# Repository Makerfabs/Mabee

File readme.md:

# Mabee Module Serial

```c++
/*
Version:		V1.1
Author:			Vincent
Create Date:	2022/10/15
Note:
		2022/10/15	V1.1: Add readme
*/
```

[toc]

# Makerfabs

[Makerfabs home page](https://www.makerfabs.com/)

[Makerfabs Wiki](https://wiki.makerfabs.com/)

# Mabee Module List

- Mabee CO2
- Mabee 6Aixs IMU MPU6050
- Mabee Button
- Mabee DHT11 sensor
- Mabee Relay 10A
- Mabee Serial WiFi
- Mabee Servo SG90
- Mabee Slide Potentimeter
- Mabee WS2812 8bit

## Mabee CO2

This Mabee module is an air quality monitor. Based on SGP30, this module provides TVOC(Total Volatile Organic Compounds) and CO2eq output; Based on the Sensirion temperature/ humidity sensors SHT31, it output highest-accuracy ±2% relative humidity and ±0.3°C accuracy temperature.

Product Link ：[Mabee_TVOC and eCO2 SGP30 & Temperature and Humidity SHT31](https://www.makerfabs.com/mabee-tvoc-and-eco2-sgp30-sht31.html)

Wiki Link : [Mabee_CO2](https://wiki.makerfabs.com/Mabee_CO2.html)

## Mabee 6Aixs IMU MPU6050

This Mabee_ MPU6050 Accelerometer& Gyro has 3-Axis digital accelerometer and 3-Axis gyroscope, suitable for common motion capturing of acceleration and Orientation.

Product Link ：[Mabee_6Aixs IMU MPU6050](https://www.makerfabs.com/mabee-6aixs-imu-mpu6050.html)

## Mabee Button

A simple button with Cap for digital inputs, with Mabee Interface for easy usage.

Product Link ：[Mabee_Button](https://www.makerfabs.com/mabee-button.html)

## Mabee DHT11 sensor

Mabee_Temperature& Humidity DHT11 is high quality, low-cost digital temperature, and humidity sensor based on the DHT11 module, which is the most commonly used sensor for temperature& Humidity, it is widely favored by hardware enthusiasts for its advantages such as low power consumption and excellent long-term stability.

Product Link ：[Mabee_Temperature& Humidity DHT11](https://www.makerfabs.com/mabee-dht11.html)

## Mabee Relay 10A

A Relay module used to control high voltage& big current circuits On/Off. It is a digital normally open switch that controls a relay capable of switching much higher voltages and currents than your normal Arduino boards. When the relay is switched on, the LED will light up and the relay will allow current to flow. The peak voltage capability is 250V at 10A.

Product Link ：[Mabee_Relay 10A](https://www.makerfabs.com/mabee-relay-10a.html)

## Mabee Serial WiFi

This Mabee Serial Wifi is based on ESP-12S, to make the WiFi available for more hardware platforms such as the Pi Pico.

Product Link ：[Mabee_Serial WiFi](https://www.makerfabs.com/mabee-serial-wifi.html)

## Mabee Servo SG90

A simple& cheap Servo module with Mabee interface, for starters to learn the servo usage and basic applications.

Product Link ：[Mabee_Servo SG90](https://www.makerfabs.com/mabee-servo-sg90.html)

## Mabee Slide Potentimeter

Do you still remember your physics class in junior middle school, about the potentiometer? The slide potentiometer could be the most basic impression for a "potentiometer".

Product Link ：[Mabee_Slide Potentiometer](https://www.makerfabs.com/mabee-slide-potentiometer.html)

## Mabee WS2812 8bit

8 pcs of WS2812 RGB LED easily for panel mounting with Mabee interface. 2 Mabee interface Input& Output, for multiple cascading.

Product Link ：[Mabee_WS2812_8bit](https://www.makerfabs.com/mabee-ws2812-8bit.html)

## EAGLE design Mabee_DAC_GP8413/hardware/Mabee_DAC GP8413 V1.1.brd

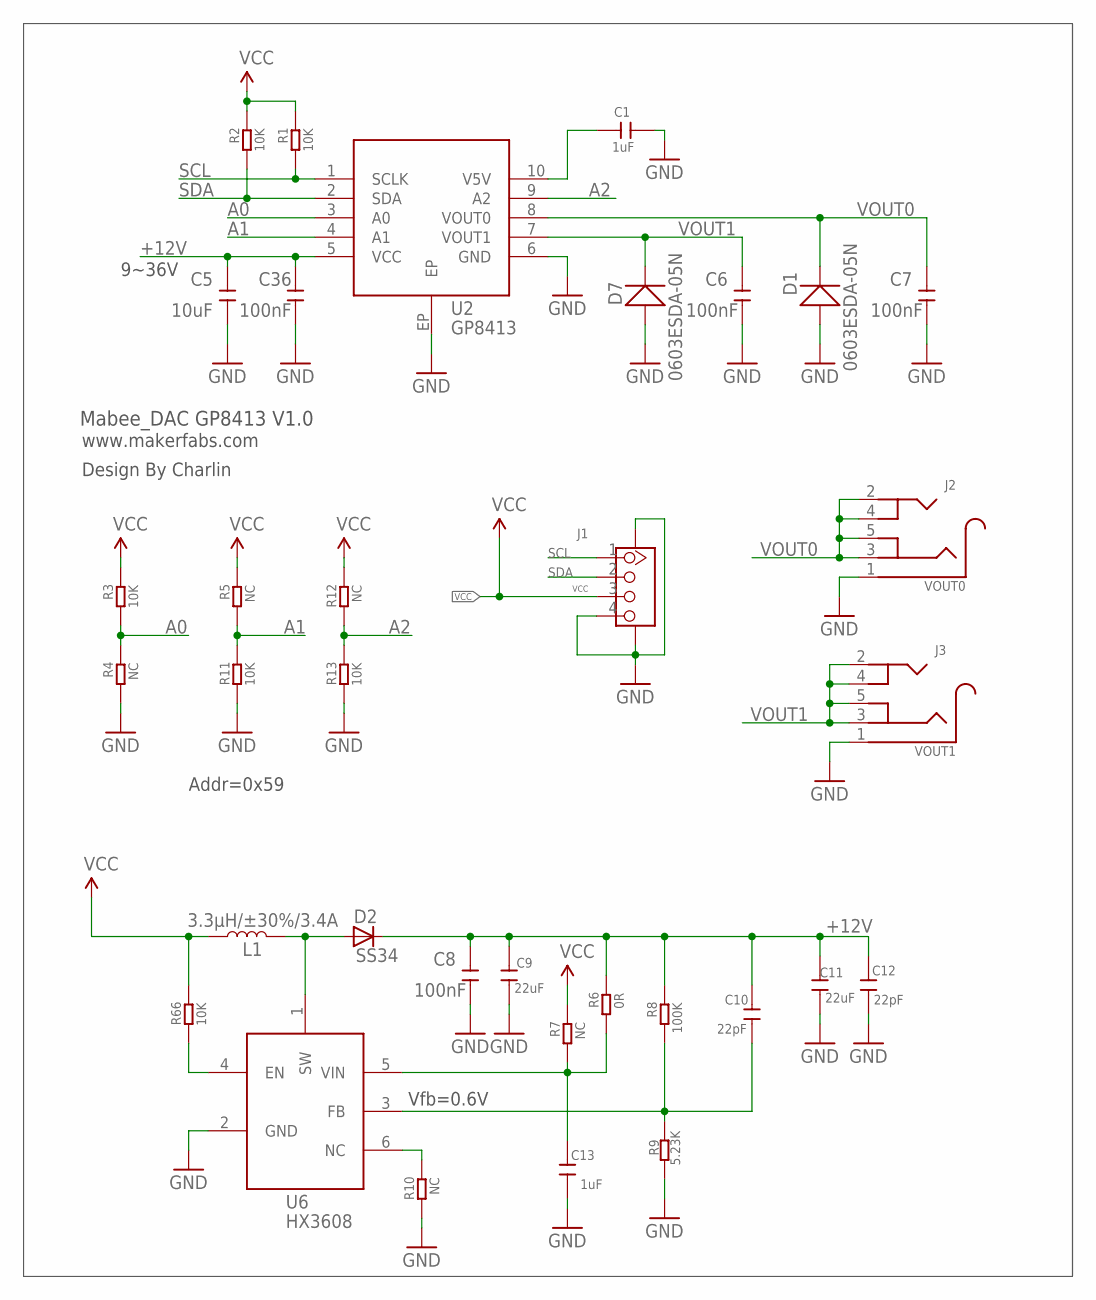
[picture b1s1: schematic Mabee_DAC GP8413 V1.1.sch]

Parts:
C1, C13: 1uF; 0603
C5: 10uF; 0603
C6, C7, C8, C36: 100nF; 0603
C9, C11: 22uF; DISCRETE_C0805
C10, C12: 22pF; 0603
D1, D7: 0603ESDA-05N; DISCRETE_SOD523
D2: SS34; DO-214AC
J1: GROVE-CONNECTOR-SMD'90D'; HW4-SMD-2.0-90D
L1: 3.3µH/±30%/3.4A; CR54
R1, R2, R3, R11, R13, R66: 10K; R0603
R4, R5, R7, R10, R12: NC; R0603
R6: 0R; R0603
R8: 100K; R0603
R9: 5.23K; R0603
U2: GP8413; ESOP-10-EP-150MIL
U6: HX3608; SOT-23-6
VOUT0: J2; 4UCONN_19269
VOUT1: J3; 4UCONN_19269

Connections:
+12V: C5.2, C8.2, C9.2, C10.2, C11.2, C12.2, C36.2, D2.C, R6.2, R8.2, U2.5 (VCC)
A0: R3.1, R4.2, U2.3 (A0)
A1: R5.1, R11.2, U2.4 (A1)
A2: R12.1, R13.2, U2.9 (A2)
ENABLE: R66.1, U6.4 (EN)
GND: C1.1, C5.1, C6.1, C7.1, C8.1, C9.1, C11.1, C12.1, C13.1, C36.1, D1.+, D7.+, J1.4, J1.SS1, J1.SS2, R4.1, R9.1, R10.1, R11.1, R13.1, U2.6 (GND), U2.EP, U6.2 (GND), VOUT0.1, VOUT1.1
unnamed: C1.2, U2.10 (V5V)
unnamed: C13.2, R6.1, R7.1, U6.5 (VIN)
unnamed: C10.1, R8.1, R9.2, U6.3 (FB)
unnamed: R10.2, U6.6 (NC)
unnamed: D2.A, L1.P$2 (2), U6.1 (SW)
SCL: J1.1, R1.1, U2.1 (SCLK)
SDA: J1.2, R2.1, U2.2 (SDA)
VCC: J1.3, L1.P$1 (1), R1.2, R2.2, R3.2, R5.2, R7.2, R12.2, R66.2
VOUT0: C7.2, D1.-, U2.8 (VOUT0), VOUT0.2, VOUT0.3, VOUT0.4, VOUT0.5
VOUT1: C6.2, D7.-, U2.7 (VOUT1), VOUT1.2, VOUT1.3, VOUT1.4, VOUT1.5

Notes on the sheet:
Mabee_DAC GP8413 V1.0
www.makerfabs.com
Vfb=0.6V
9~36V
Addr=0x59
Design By Charlin

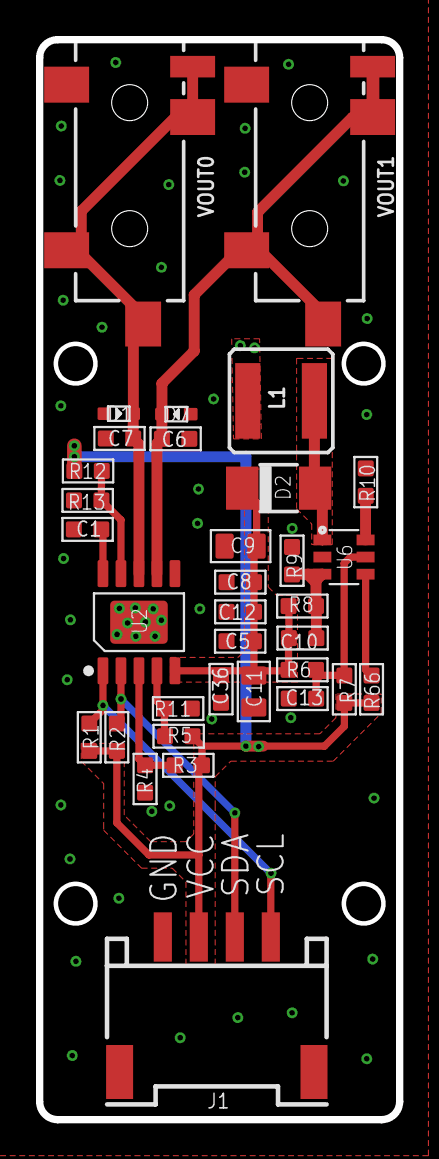
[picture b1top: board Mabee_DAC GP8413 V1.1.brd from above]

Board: 2 copper layers, 20.0 x 60.0 mm, 35 parts (1 on the bottom side), 16 nets.

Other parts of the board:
U$1: MAKERFABS_0.3

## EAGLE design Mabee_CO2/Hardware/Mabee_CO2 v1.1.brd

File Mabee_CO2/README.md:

# Mabee_CO2
Mabee_TVOC and eCO2 SGP30 &amp; Temperature and Humidity SHT31

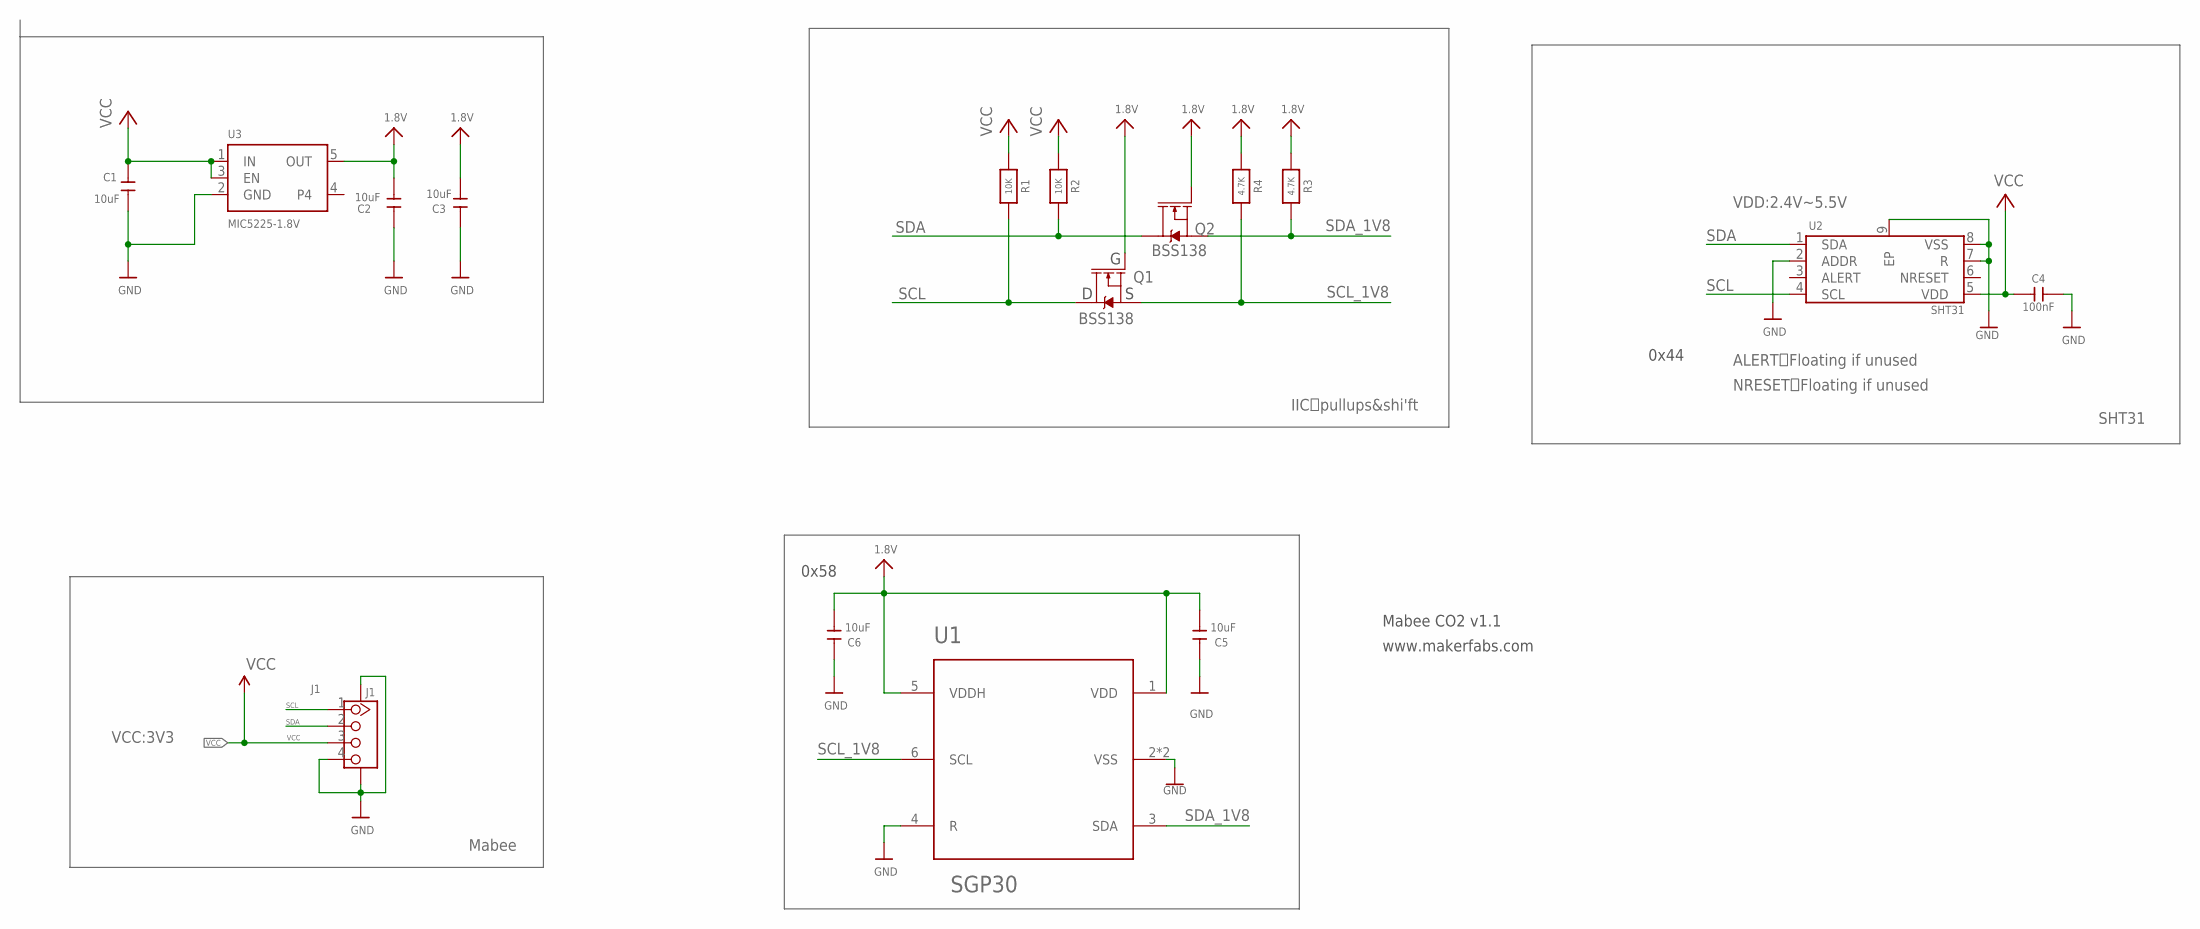
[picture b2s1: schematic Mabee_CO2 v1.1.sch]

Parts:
C1, C2, C3, C5, C6: 10uF; 0603
C4: 100nF; 0603
J1: J1; HW4-SMD-2.0-90D
Q1, Q2: BSS138; SOT23-3
R1, R2: 10K; 0603-NO
R3, R4: 4.7K; 0603-NO
U1: SGP30
U2: SHT31; DFN-8(3X3)_EP
U3: MIC5225-1.8V; SOT23-5

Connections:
1.8V: C2.1, C3.1, C5.1, C6.1, Q1.1 (G), Q2.1 (G), R3.1, R4.1, U1.1 (VDD), U1.5 (VDDH), U3.5 (OUT)
GND: C1.2, C2.2, C3.2, C4.2, C5.2, C6.2, J1.4, J1.SS1, J1.SS2, U1.2 (VSS), U1.4 (R), U1.P$7 (VSS), U2.2 (ADDR), U2.7 (R), U2.8 (VSS), U2.9 (EP), U3.2 (GND)
SCL: J1.1, Q1.3 (D), R1.2, U2.4 (SCL)
SCL_1V8: Q1.2 (S), R4.2, U1.6 (SCL)
SDA: J1.2, Q2.3 (D), R2.2, U2.1 (SDA)
SDA_1V8: Q2.2 (S), R3.2, U1.3 (SDA)
VCC: C1.1, C4.1, J1.3, R1.1, R2.1, U2.5 (VDD), U3.1 (IN), U3.3 (EN)

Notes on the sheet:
Mabee
SHT31
IIC pullups&shi'ft
Mabee CO2 v1.1
www.makerfabs.com
VCC:3V3
VDD:2.4V~5.5V
ALERT：Floating if unused
NRESET：Floating if unused
0x58
0x44

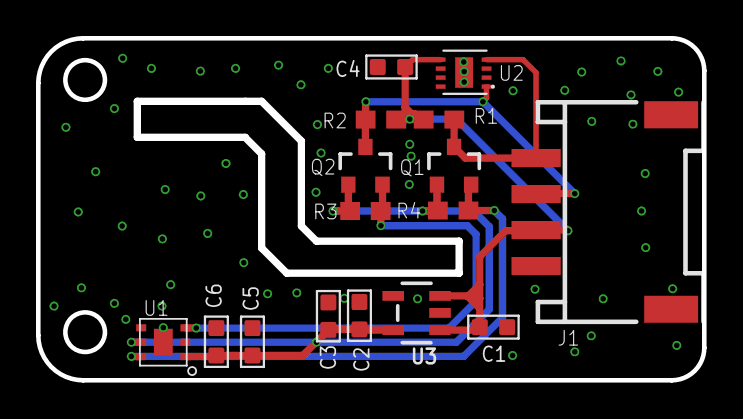
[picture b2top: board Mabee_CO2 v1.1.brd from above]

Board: 2 copper layers, 36.8 x 18.8 mm, 17 parts (1 on the bottom side), 7 nets.

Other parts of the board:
U$10: MAKERFABS_0.3

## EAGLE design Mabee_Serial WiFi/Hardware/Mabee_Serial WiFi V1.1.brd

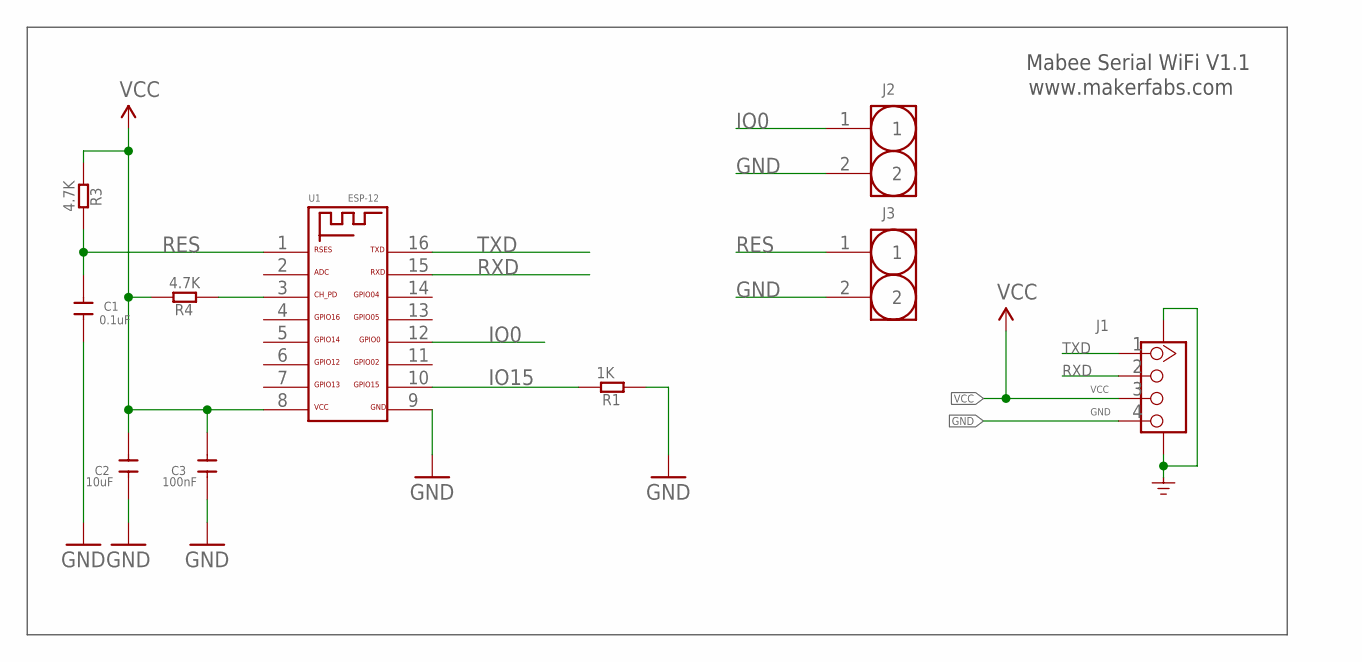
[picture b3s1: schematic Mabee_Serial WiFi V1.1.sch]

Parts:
C1: 0.1uF; C0603
C2: 10uF; C0603
C3: 100nF; C0603
J1: GROVE-CONNECTOR-SMD'90D'; HW4-SMD-2.0-90D
J2, J3: HEADER-2P-65/35MIL; 2P-2.54-65/35MIL
R1: 1K; 0603
R3, R4: 4.7K; 0603
U1: ESP-12

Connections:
EN: R4.1, U1.3
GND: C1.2, C2.2, C3.2, J1.4, J1.SS1, J1.SS2, J2.2, J3.2, R1.1, U1.9
IO0: J2.1, U1.12
IO15: R1.2, U1.10
RES: C1.1, J3.1, R3.2, U1.1
RXD: J1.2, U1.15
TXD: J1.1, U1.16
VCC: C2.1, C3.1, J1.3, R3.1, R4.2, U1.8

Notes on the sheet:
Mabee Serial WiFi V1.1
www.makerfabs.com

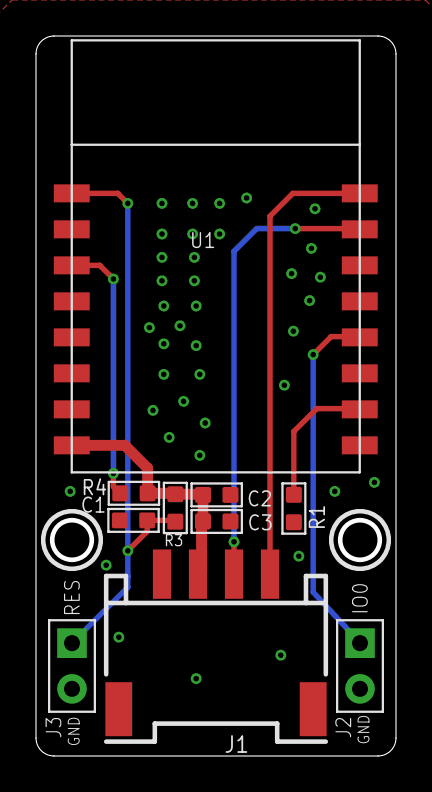
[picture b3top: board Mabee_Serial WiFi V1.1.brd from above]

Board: 2 copper layers, 19.7 x 39.7 mm, 11 parts (1 on the bottom side), 8 nets.

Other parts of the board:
U$2: MAKERFABS_0.3

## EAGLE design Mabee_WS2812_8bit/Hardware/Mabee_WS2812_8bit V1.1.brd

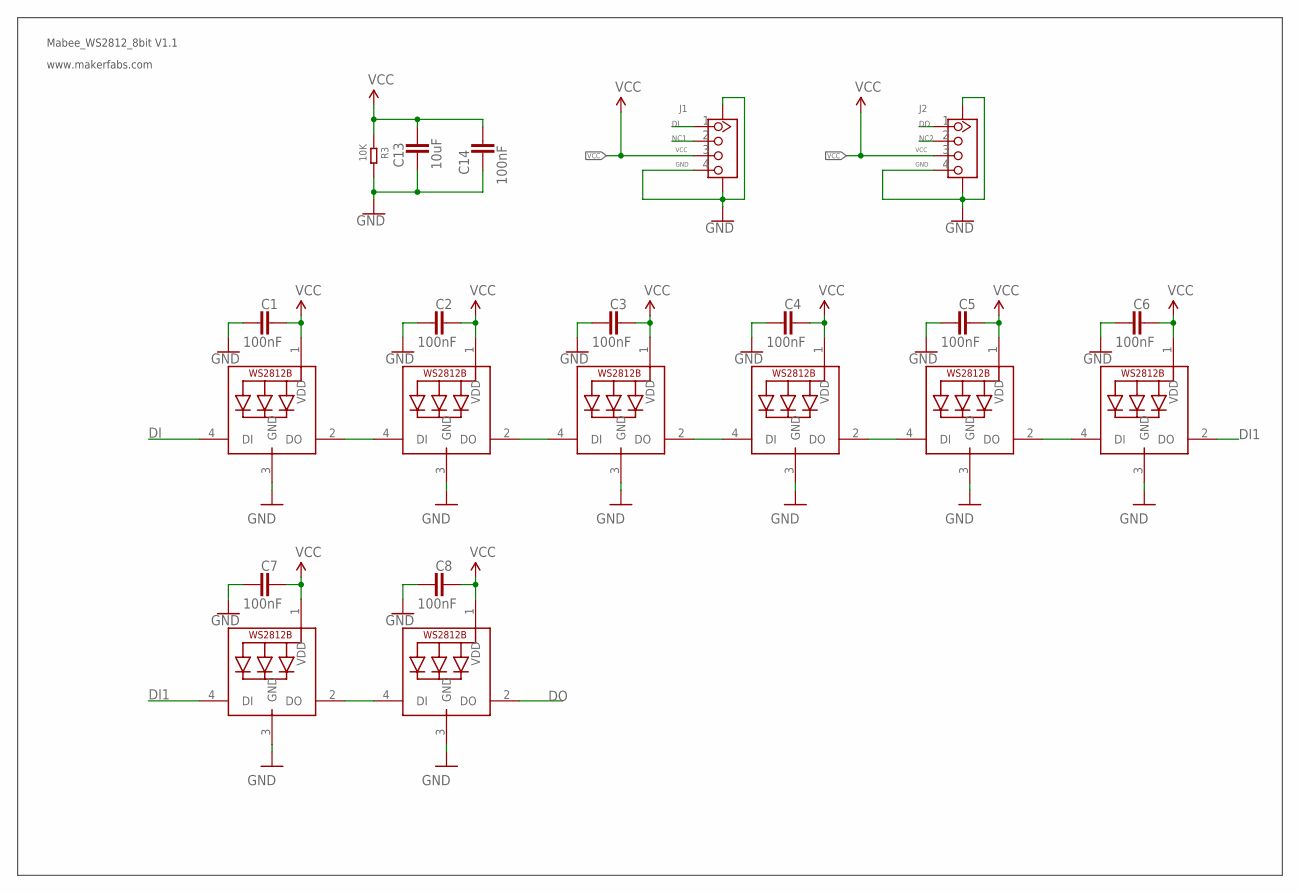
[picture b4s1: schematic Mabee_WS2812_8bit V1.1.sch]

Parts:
C1, C2, C3, C4, C5, C6, C7, C8, C14: 100nF; C0603
C13: 10uF; C0603
J1, J2: GROVE-CONNECTOR-SMD'90D'; HW4-SMD-2.0-90D
LED0, LED1, LED2, LED3, LED4, LED5, LED6, LED7: WS2812B3535; LED3535
R3: 10K; R0603

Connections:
DI: J1.1, LED0.4 (DI)
DI1: LED5.2 (DO), LED6.4 (DI)
DO: J2.1, LED7.2 (DO)
GND: C1.1, C2.1, C3.1, C4.1, C5.1, C6.1, C7.1, C8.1, C13.1, C14.1, J1.4, J1.SS1, J1.SS2, J2.4, J2.SS1, J2.SS2, LED0.3 (GND), LED1.3 (GND), LED2.3 (GND), LED3.3 (GND), LED4.3 (GND), LED5.3 (GND), LED6.3 (GND), LED7.3 (GND), R3.2
unnamed: LED0.2 (DO), LED1.4 (DI)
unnamed: LED1.2 (DO), LED2.4 (DI)
unnamed: LED2.2 (DO), LED3.4 (DI)
unnamed: LED3.2 (DO), LED4.4 (DI)
unnamed: LED4.2 (DO), LED5.4 (DI)
unnamed: LED6.2 (DO), LED7.4 (DI)
NC1: J1.2
NC2: J2.2
VCC: C1.2, C2.2, C3.2, C4.2, C5.2, C6.2, C7.2, C8.2, C13.2, C14.2, J1.3, J2.3, LED0.1 (VDD), LED1.1 (VDD), LED2.1 (VDD), LED3.1 (VDD), LED4.1 (VDD), LED5.1 (VDD), LED6.1 (VDD), LED7.1 (VDD), R3.1

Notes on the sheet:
Mabee_WS2812_8bit V1.1
www.makerfabs.com

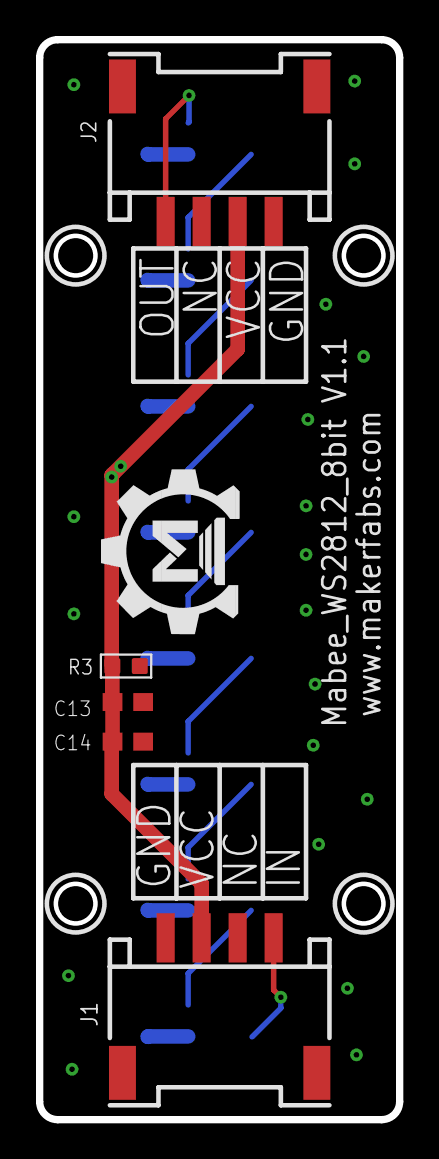
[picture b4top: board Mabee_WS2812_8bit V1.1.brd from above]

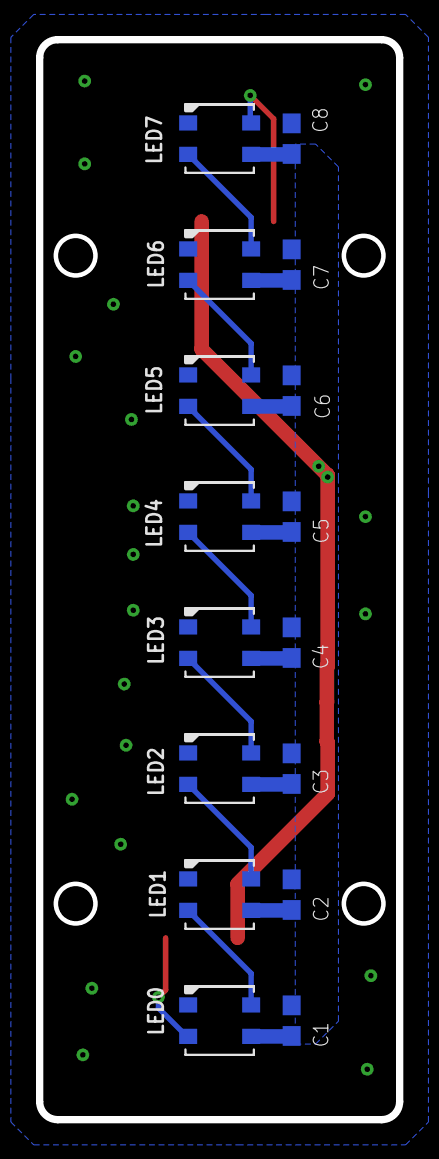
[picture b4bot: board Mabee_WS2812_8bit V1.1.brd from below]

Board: 2 copper layers, 20.0 x 60.0 mm, 22 parts (16 on the bottom side), 11 nets.

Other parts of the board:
U$2: MAKERFABS_0.3

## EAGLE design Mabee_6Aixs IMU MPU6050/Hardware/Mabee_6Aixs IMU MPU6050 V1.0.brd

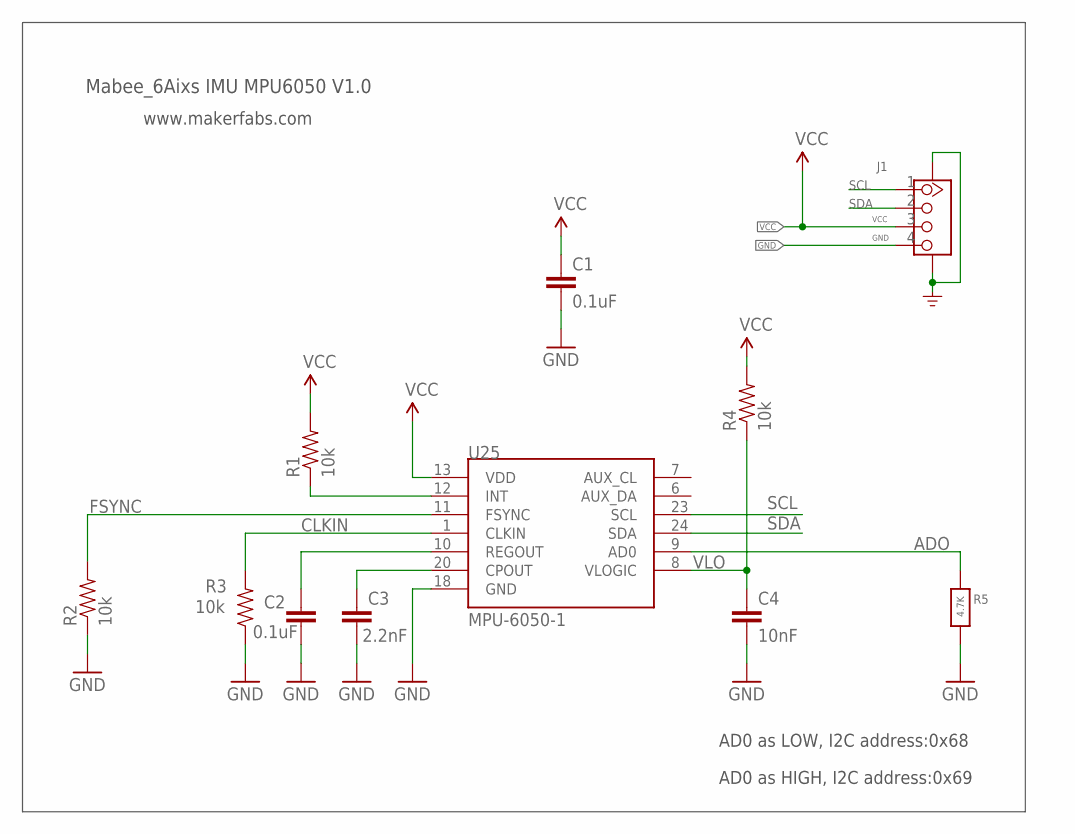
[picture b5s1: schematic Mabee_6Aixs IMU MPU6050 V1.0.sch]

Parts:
C1, C2: 0.1uF; 0603-CAP
C3: 2.2nF; 0603-CAP
C4: 10nF; 0603-CAP
J1: GROVE-CONNECTOR-SMD'90D'; HW4-SMD-2.0-90D
R1, R2, R3, R4: 10k; 0603-RES
R5: 4.7K; 0603-NO
U25: MPU-6050-1; QFN-24-4MM2

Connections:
ADO: R5.1, U25.9 (AD0)
CLKIN: R3.2, U25.1 (CLKIN)
FSYNC: R2.2, U25.11 (FSYNC)
GND: C1.2, C2.2, C3.2, C4.2, J1.4, J1.SS1, J1.SS2, R2.1, R3.1, R5.2, U25.18 (GND)
IO35: R1.1, U25.12 (INT)
unnamed: C3.1, U25.20 (CPOUT)
unnamed: C2.1, U25.10 (REGOUT)
SCL: J1.1, U25.23 (SCL)
SDA: J1.2, U25.24 (SDA)
VCC: C1.1, J1.3, R1.2, R4.2, U25.13 (VDD)
VLO: C4.1, R4.1, U25.8 (VLOGIC)

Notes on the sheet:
Mabee_6Aixs IMU MPU6050 V1.0
AD0 as LOW, I2C address:0x68
AD0 as HIGH, I2C address:0x69
www.makerfabs.com

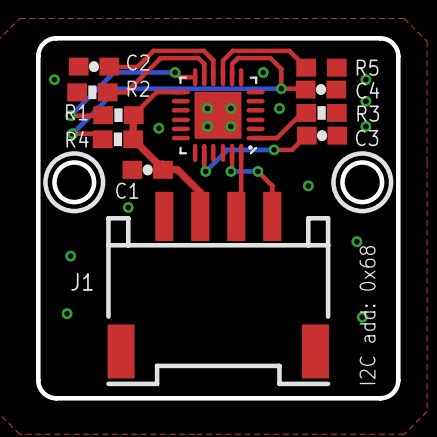
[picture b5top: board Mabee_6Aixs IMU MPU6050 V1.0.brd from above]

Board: 2 copper layers, 20.0 x 20.0 mm, 12 parts (1 on the bottom side), 11 nets.

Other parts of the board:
U$1: MAKERFABS_0.3

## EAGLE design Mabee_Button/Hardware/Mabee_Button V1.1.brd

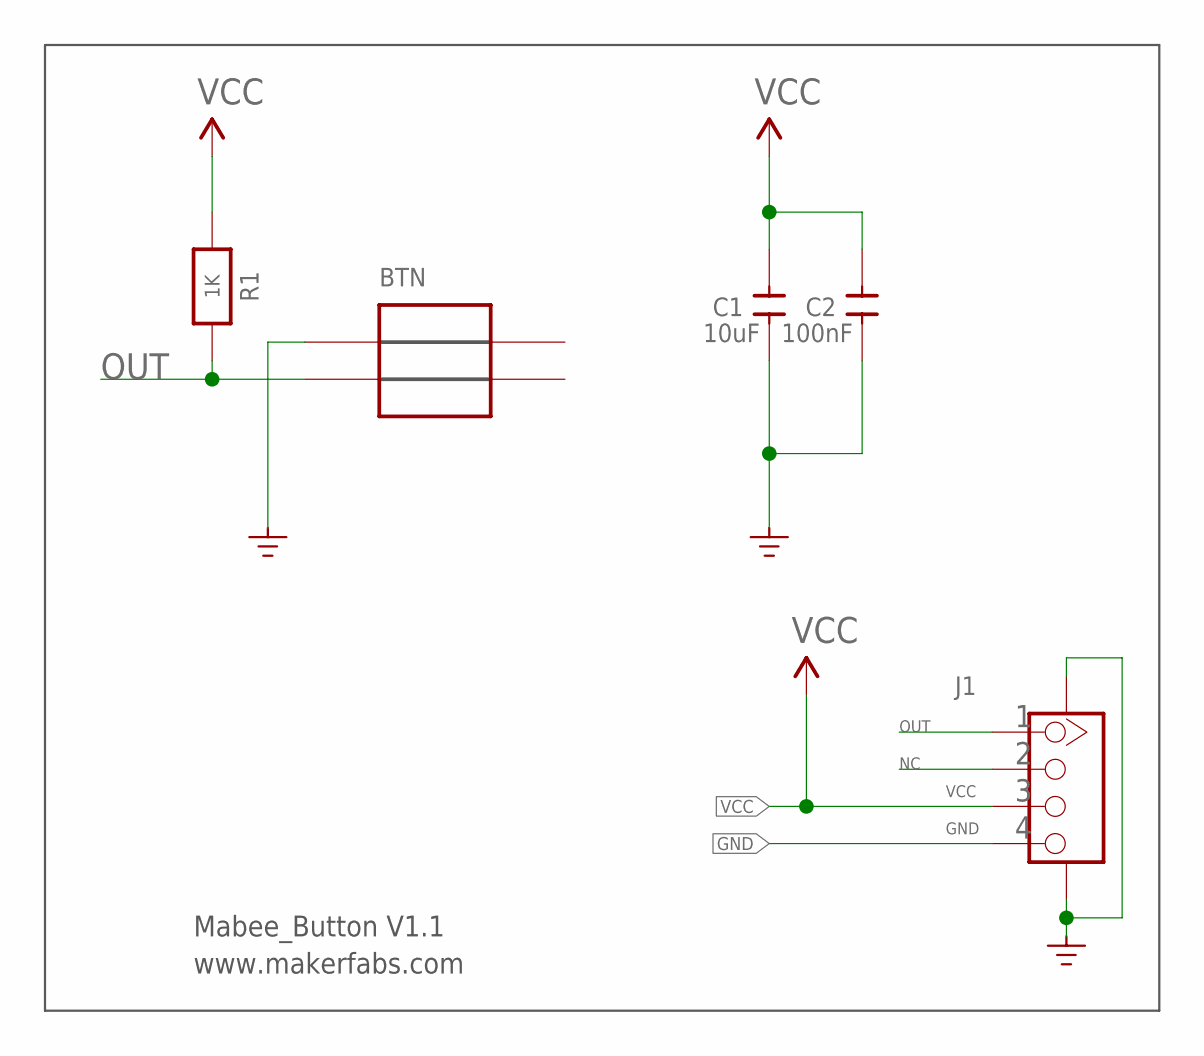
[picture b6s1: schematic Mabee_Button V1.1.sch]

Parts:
BTN: BUTTON_1212; 12*12_BUTTON_DIP
C1: 10uF; 0603
C2: 100nF; 0603
J1: GROVE-CONNECTOR-SMD'90D'; HW4-SMD-2.0-90D
R1: 1K; 0603-NO

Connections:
GND: BTN.1, C1.1, C2.1, J1.4, J1.SS1, J1.SS2
NC: J1.2
OUT: BTN.3, J1.1, R1.2
VCC: C1.2, C2.2, J1.3, R1.1

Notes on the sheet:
Mabee_Button V1.1
www.makerfabs.com

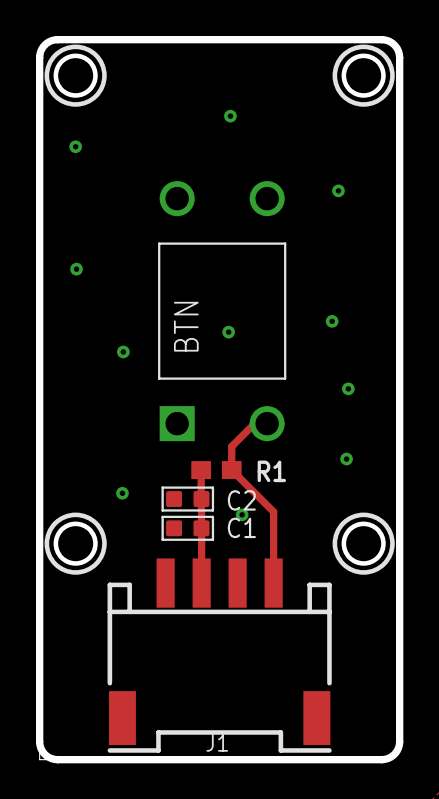
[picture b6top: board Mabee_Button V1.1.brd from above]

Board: 2 copper layers, 20.0 x 40.0 mm, 6 parts (1 on the bottom side), 3 nets.

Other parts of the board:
U$3: MAKERFABS_0.3

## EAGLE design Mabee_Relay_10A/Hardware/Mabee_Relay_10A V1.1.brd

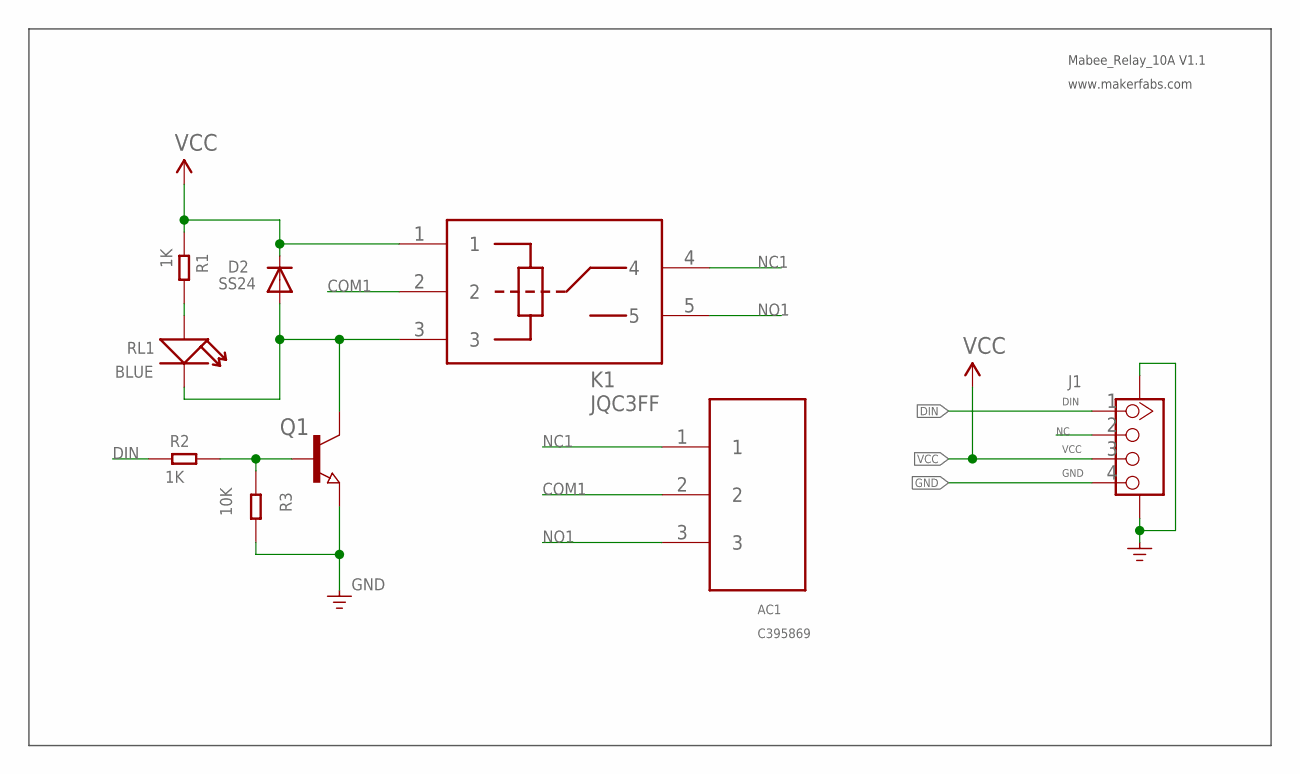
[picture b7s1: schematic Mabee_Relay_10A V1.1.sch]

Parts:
AC1: C395869; PIN_3P
D2: SS24; SMADIODE
J1: GROVE-CONNECTOR-SMD'90D'; HW4-SMD-2.0-90D
K1: JQC3FF; DIP5_JQC3FF
Q1: NPN-TRANSISTOR_SOT23; SOT23
R1, R2: 1K; R0603
R3: 10K; R0603
RL1: BLUE; LED-0603

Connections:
COM1: AC1.2, K1.2
DIN: J1.1, R2.1
GND: J1.4, J1.SS1, J1.SS2, Q1.2 (E), R3.2
unnamed: R1.2, RL1.+
unnamed: D2.A, K1.3, Q1.3 (C), RL1.-
unnamed: Q1.1 (B), R2.2, R3.1
NC: J1.2
NC1: AC1.1, K1.4
NO1: AC1.3, K1.5
VCC: D2.C, J1.3, K1.1, R1.1

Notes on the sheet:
Mabee_Relay_10A V1.1
www.makerfabs.com

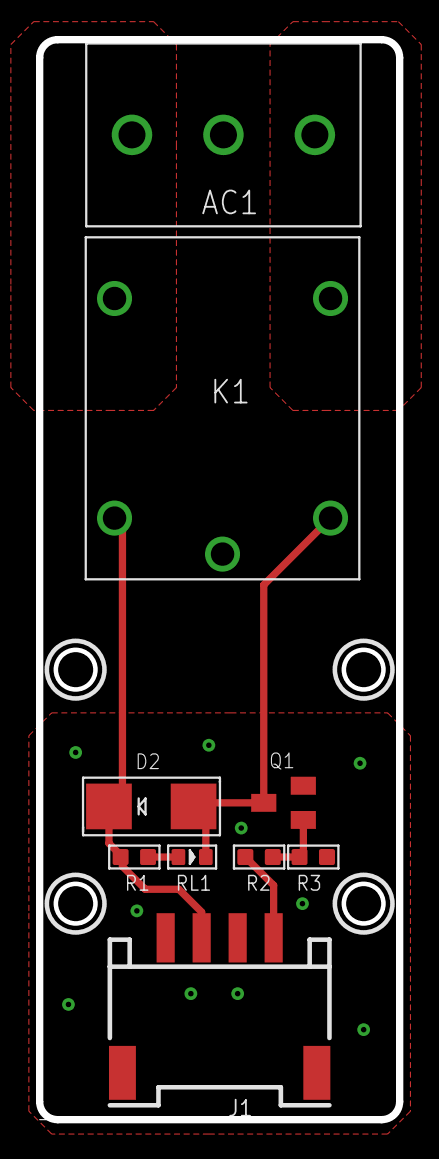
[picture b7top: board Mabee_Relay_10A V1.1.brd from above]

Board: 2 copper layers, 20.0 x 60.0 mm, 10 parts (1 on the bottom side), 9 nets.

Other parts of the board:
U$2: MAKERFABS_0.3

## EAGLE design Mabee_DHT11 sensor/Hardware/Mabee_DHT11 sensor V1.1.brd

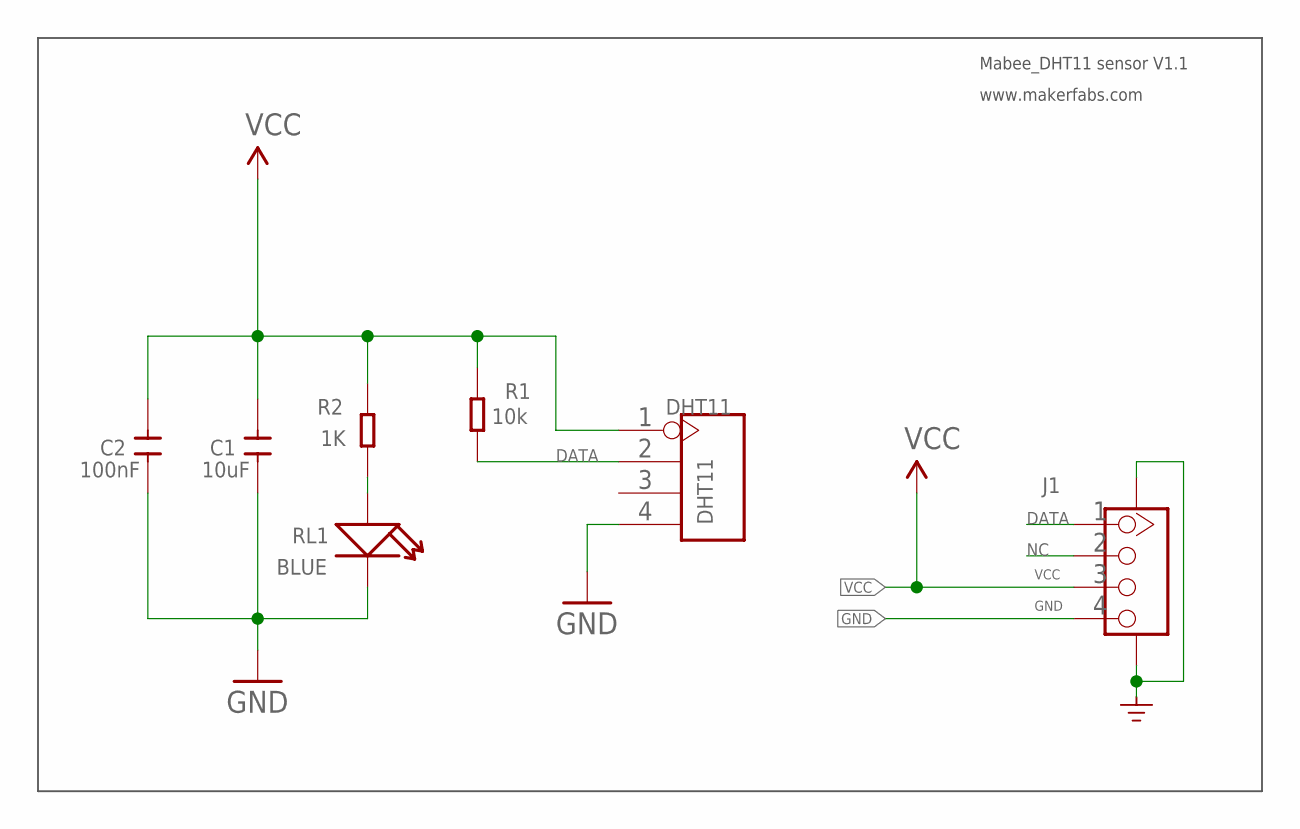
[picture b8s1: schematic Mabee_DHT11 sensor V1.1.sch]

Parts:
C1: 10uF; 0603
C2: 100nF; 0603
DHT11: DHT11; 4P-65/35ROUND
J1: GROVE-CONNECTOR-SMD'90D'; HW4-SMD-2.0-90D
R1: 10k; R0603
R2: 1K; R0603
RL1: BLUE; LED-0603

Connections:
DATA: DHT11.2, J1.1, R1.1
GND: C1.1, C2.1, DHT11.4, J1.4, J1.SS1, J1.SS2, RL1.-
unnamed: R2.2, RL1.+
NC: J1.2
VCC: C1.2, C2.2, DHT11.1, J1.3, R1.2, R2.1

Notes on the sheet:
Mabee_DHT11 sensor V1.1
www.makerfabs.com

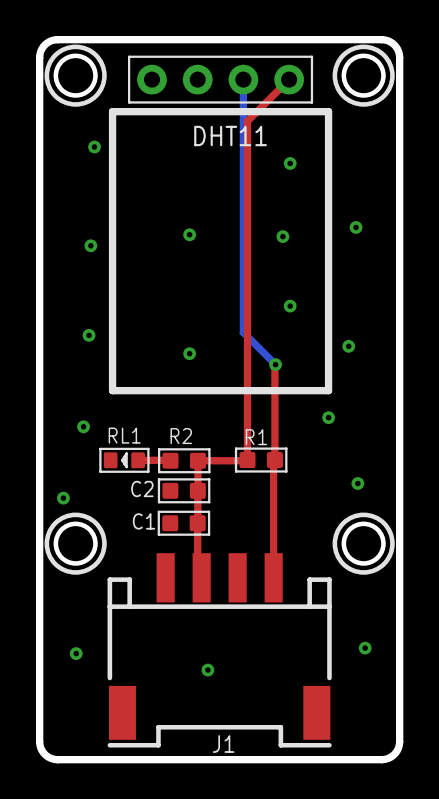
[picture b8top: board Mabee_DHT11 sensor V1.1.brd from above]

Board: 2 copper layers, 20.0 x 40.0 mm, 8 parts (1 on the bottom side), 4 nets.

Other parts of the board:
U$2: MAKERFABS_0.3

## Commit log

2021-04-13 Create
2021-04-13 change
2021-05-09 create gyro ws2812
2021-05-13 add serial wifi
2021-05-22 create servo ranging
2022-10-15 Add Mabee CO2
2022-11-23 Update Wiki Link
2024-06-28 Add Mabee DAC

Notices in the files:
parts and their libraries:
microbuilder: This work is placed in the public domain, and may be freely used for commercial and non-commercial work with the following conditions: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
SparkFun-Aesthetics: Licensing: Creative Commons ShareAlike 4.0 International - https://creativecommons.org/licenses/by-sa/4.0
